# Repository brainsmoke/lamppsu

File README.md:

# ceiling mounted AC/DC converter

Using [Flame retardant filament](https://www.formfutura.com/filaments/petg/premium-petg-flame-retardant) for the
3d-printed parts.

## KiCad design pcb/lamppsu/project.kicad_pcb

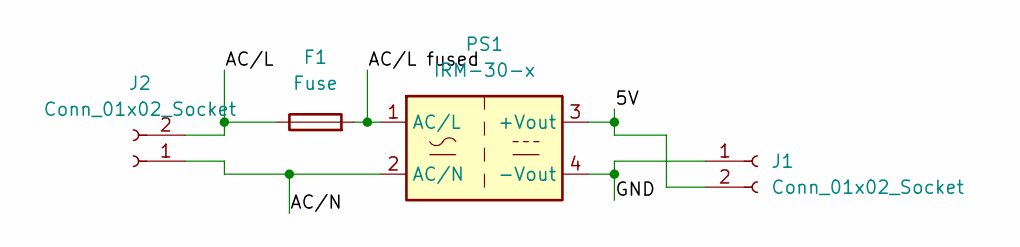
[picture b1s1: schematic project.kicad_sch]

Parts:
F1: Fuse; PTF75
J1, J2: Conn_01x02_Socket; WAGO_2604-1102
PS1: IRM-30-x; MeanWell_IRM-30

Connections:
/5V: J1.2, PS1.3 (+Vout)
/AC/L: F1.1, J2.2
/AC/L fused: F1.2, PS1.1 (AC/L)
/AC/N: J2.1, PS1.2 (AC/N)
/GND: J1.1, PS1.4 (-Vout)

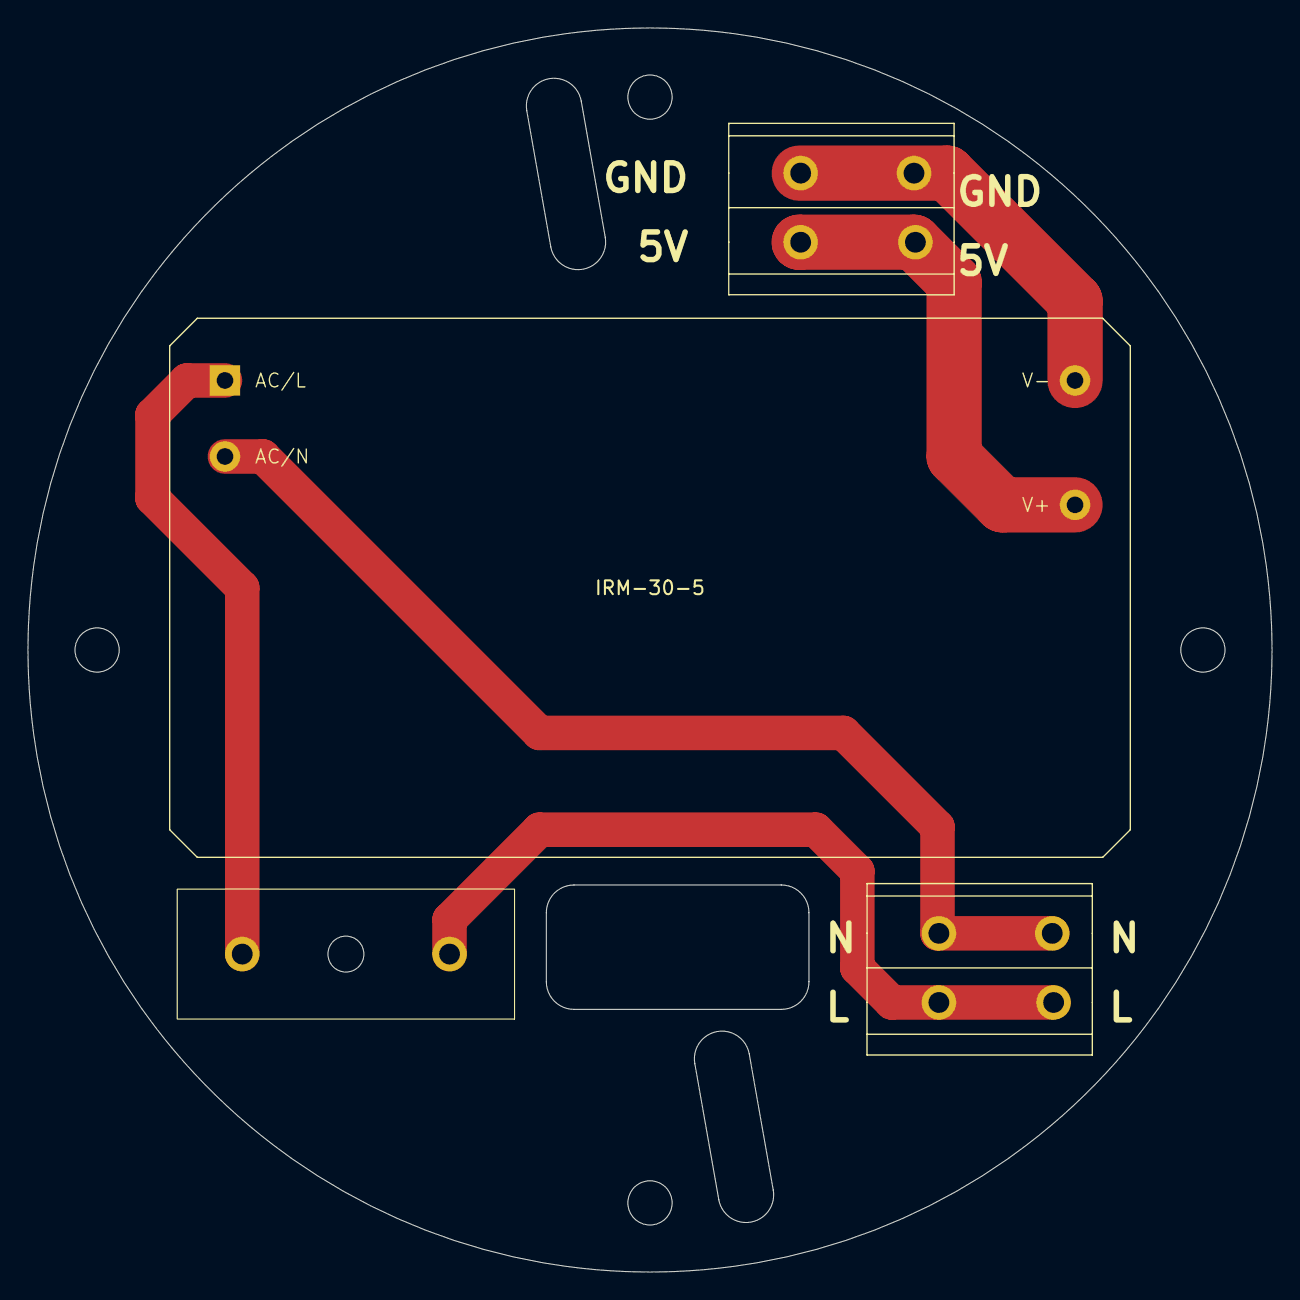
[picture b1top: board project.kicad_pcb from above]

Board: 2 copper layers, 90.0 x 90.0 mm, 4 parts (0 on the bottom side), 5 nets.

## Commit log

2026-03-20 untested
2026-03-20 readme
2026-03-20 typo
2026-03-20 md syntax
2026-03-28 fix footprint
2026-04-03 add 3d model
2026-04-03 correct 0.1mm mistake in wago footprint
2026-04-04 add cover
2026-04-05 adjust hole size, change print orentation
2026-04-05 add fillet
2026-04-06 add material comment
2026-04-06 shrink cable diameter
2026-04-29 use more recent makefile
2026-05-10 add images
2026-05-10 remove untested
